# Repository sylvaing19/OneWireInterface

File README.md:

# OneWireInterface
Implements the Dynamixel 1.0 protocol to communicate on half-duplex UART with any compatible device

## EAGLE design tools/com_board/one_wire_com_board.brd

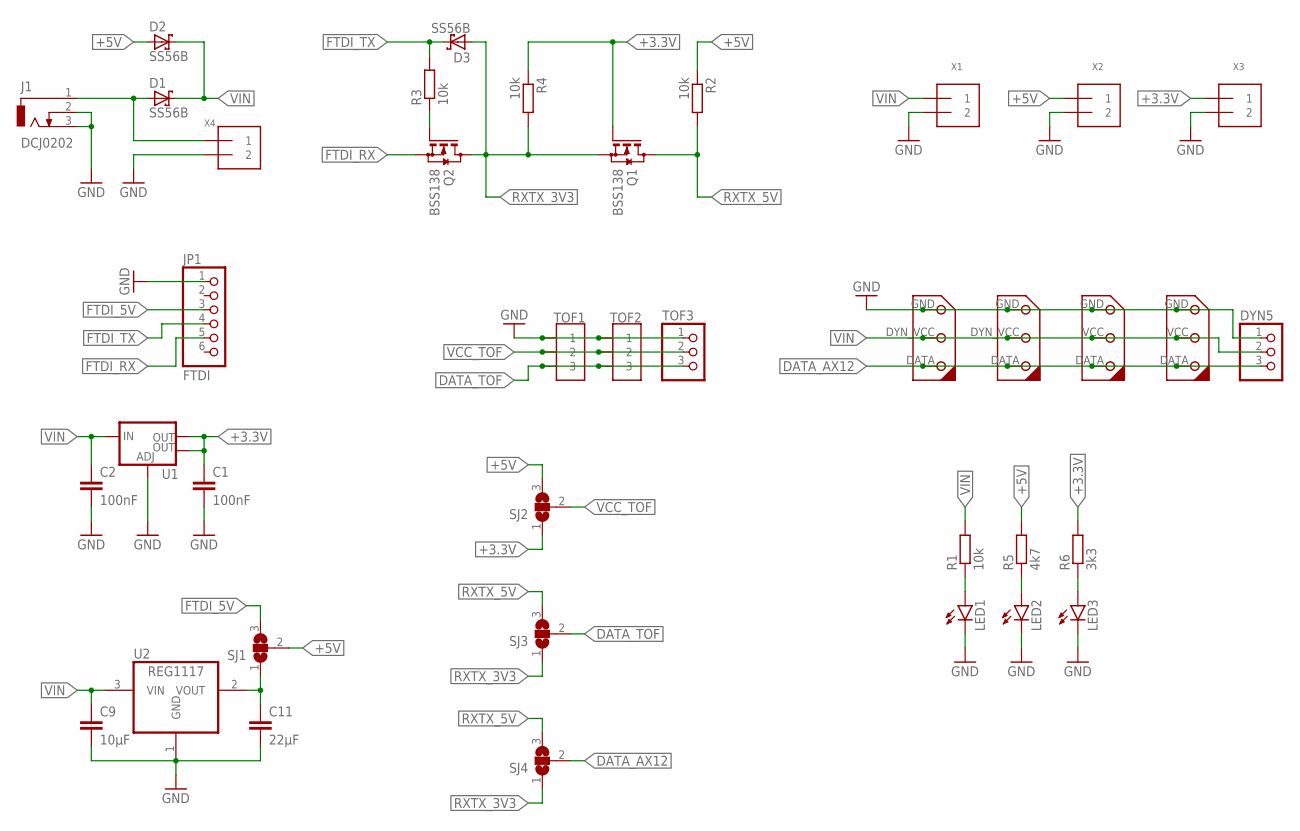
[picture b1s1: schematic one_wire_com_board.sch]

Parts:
C1, C2: 100nF; C0805; PARTNO *
C9: 10µF; C0805
C11: 22µF; C0805
D1, D2, D3: SS56B; SMB
DYN1, DYN2: DYNAMIXEL-1X03AX; DYNAMIXEL_AX_1X03
DYN3, DYN4: DYNAMIXEL-1X03XL; DYNAMIXEL_XL_1X03
DYN5: PINHD-1X3; 1X03
J1: DCJ0202
JP1: FTDI; 1X06/90
LED1, LED2, LED3: LEDSMT1206; 1206
Q1, Q2: BSS138; SOT23
R1, R2, R3, R4: 10k; R0805
R5: 4k7; R0805
R6: 3k3; R0805
SJ1, SJ2, SJ3, SJ4: SJ2W; SJ_2
TOF1, TOF2: JST-03; GH-03-V
TOF3: PINHD-1X3; 1X03
U1: V_REG_LM1117SOT223; SOT223; PARTNO *
U2: REG1117; SOT223
X1, X2, X3, X4: TERMBLOCK_1X2; TERMBLOCK_1X2-3.5MM

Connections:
+3.3V: C1.1, Q1.1 (G), R4.1, R6.2, SJ2.1, U1.2 (OUT), U1.4 (OUT), X3.1
+5V: D2.A, R2.1, R5.2, SJ1.2, SJ2.3, X2.1
DATA_AX12: DYN1.DATA, DYN2.DATA, DYN3.DATA, DYN4.DATA, DYN5.3, SJ4.2
DATA_TOF: SJ3.2, TOF1.3, TOF2.3, TOF3.3
FTDI_5V: JP1.3, SJ1.3
FTDI_RX: JP1.5, Q2.2 (S)
FTDI_TX: D3.C, JP1.4, R3.2
GND: C1.2, C2.2, C9.2, C11.2, DYN1.GND, DYN2.GND, DYN3.GND, DYN4.GND, DYN5.1, J1.2, J1.3, JP1.1, LED1.C, LED2.C, LED3.C, TOF1.1, TOF2.1, TOF3.1, U1.1 (ADJ), U2.1 (GND), X1.2, X2.2, X3.2, X4.2
unnamed: D1.A, J1.1, X4.1
unnamed: LED1.A, R1.1
unnamed: C11.1, SJ1.1, U2.2 (VOUT)
unnamed: Q2.1 (G), R3.1
unnamed: LED2.A, R5.1
unnamed: LED3.A, R6.1
RXTX_3V3: D3.A, Q1.2 (S), Q2.3 (D), R4.2, SJ3.1, SJ4.1
RXTX_5V: Q1.3 (D), R2.2, SJ3.3, SJ4.3
VCC_TOF: SJ2.2, TOF1.2, TOF2.2, TOF3.2
VIN: C2.1, C9.1, D1.C, D2.C, DYN1.DYN_VCC, DYN2.DYN_VCC, DYN3.VCC (DYN_VCC), DYN4.VCC (DYN_VCC), DYN5.2, R1.2, U1.3 (IN), U2.3 (VIN), X1.1

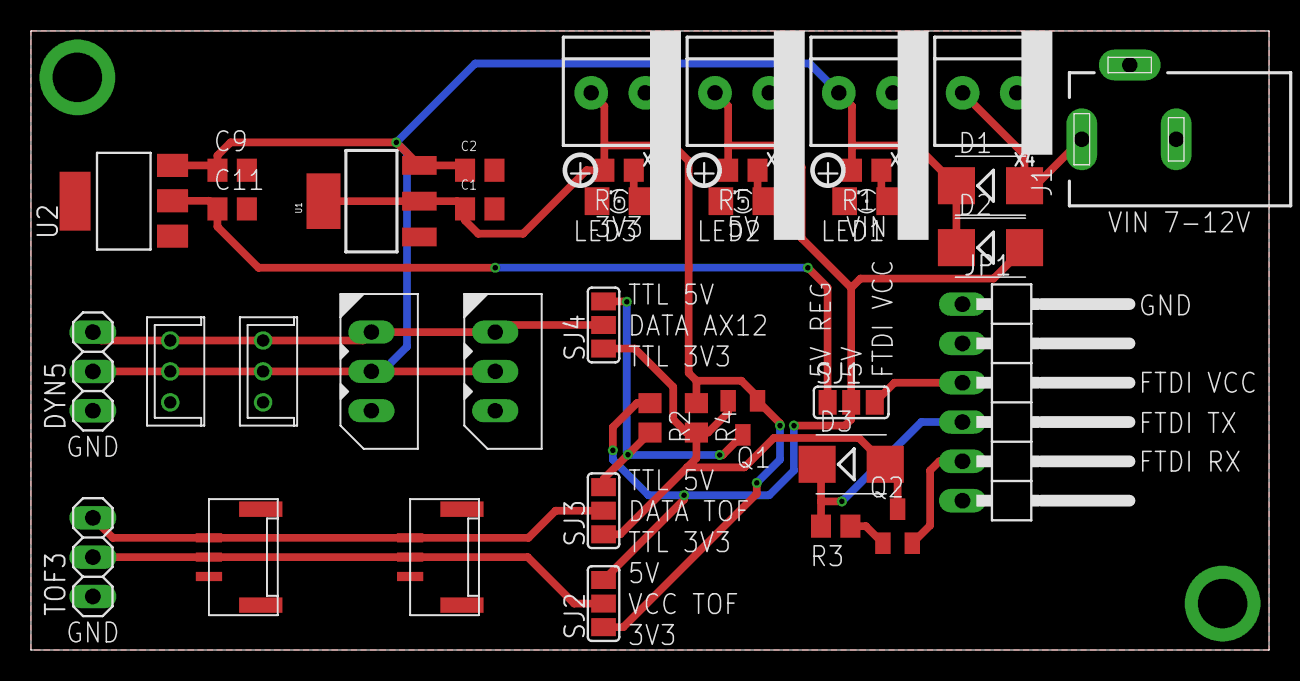
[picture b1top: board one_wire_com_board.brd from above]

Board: 2 copper layers, 80.0 x 40.0 mm, 38 parts (0 on the bottom side), 18 nets.

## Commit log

2019-09-01 initial version
2019-09-01 improved error handling on master side
2019-09-03 Slave interface: small changes in getters/setters
2019-09-12 start gui tool project
2019-09-12 python tool: start to develop gui
2019-09-12 python-tool: add communication module
2019-09-12 python-tool: continue to implement gui
2019-09-14 python tool: first functionnal version
2019-09-20 python-tool: add reg map for AX12
2020-03-09 hardware: add ref for FTDI cable
2020-03-09 OneWireInterface: add debug Stream
2020-03-09 add PCB drawing, to connect easily a one-wire device to a computer
2020-03-09 add .gitignore for Eagle

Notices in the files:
parts and their libraries:
SparkFun-PowerIC: Licensing: Creative Commons ShareAlike 4.0 International - https://creativecommons.org/licenses/by-sa/4.0
microbuilder: This work is placed in the public domain, and may be freely used for commercial and non-commercial work with the following conditions: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
